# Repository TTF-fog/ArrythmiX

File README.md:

# Main Repo
> For Blueprint Reviewers, [Final Version](Hardware/CAD/the_last_one.step) is what our end CAD model is. Design is goose.f3d present in the same file. BOM is present in root dir, [table format](#BOM) (collapsed) at bottom of readme and [PCB folder](Hardware/PCB). PCB Folder contains gerbers.zip and design files. Firmware is in [firmware](src) and software in [software](scripts). Everything else is in ML or doc. Check [Sections](#sections) for descriptions. thank you for reviewing our project :)

This is the main repo for the Arryhtmix Project, which aims to develop a novel, end-to-end framework for
the prediction of cardiac events

>
> We have developed a novel end to end pipeline for the prediction of cardiac arrests through machine learning alongside a medical device to facilitate the collection of data for the model.
>
>The initial process takes place on the device. The single-lead AD8232 Sensor with integrated hardware high pass and low pass filters collects ECG Data from one lead with one electrode for common mode rejection. The data is read at a rate of 360 Hz by the nRF52840 using a 12-bit ADC and concurrently denoised through an integrated LSM6DS3. While the device is idle, it is kept in deep sleep mode, significantly reducing power consumption.
>Upon the collection of 10 data points, the buffer is dispatched using BLE to the host device.
> 
>Upon being dispatched to the host device, two models are run on it. First, an Arrhythmia classification model based on the MIT-BIH dataset and architected with a BiLSTM and Random Forest classifier returns a dataclass which describes the type of arrhythmia if any. Secondly, a novel hybrid CNN-LSTM model trained on the Sudden Cardiac Arrest Holter Database predicts ventricular fibrillation risk across four temporal categories. The models have been quantised for edge deployment and offer platform flexibility. A f-score of 99 percent and of 85 percent is obtained from both models respectively.
>
- ISEF Abstract
### Sections
- [Scripts](scripts)
  - [Miscellaneous](scripts/misc)
    - mixture of normal and vibecoded scripts made for testing
  - [Rerun](scripts/rerun)
    - Scripts and Blueprints for the [Rerun](https://rerun.io) visualizer
- [Hardware](Hardware)
  - [PCB Documents](Hardware/PCB)
  - [CAD Files](Hardware/CAD)
    - all of these are from some iteration or the other, but they should represent the totality of our cad.
    - [Final Version](Hardware/CAD/the_last_one.step) is what our end model is. Design is goose.f3d present in the same file
- [Firmware](src)
  - firmware for the device
- [ML](ML)
  - Our own model training stuff, and tweaked versions of other's
- [Documentation](Doc) 
  - Extra stuff relating to the project. Will add slide decks soon:tm:
### Images 
<details>

<summary> Machine Learning </summary>

> Confusion Matrix

<br>

> train and valuation graphs

<br>

</details>

<details>

<summary>Software</summary>

Machine

<br>

</details>

<details>

<summary>Hardware</summary>

> unsoldered, sorry for bad quality

<br>

</details>

<details>

<summary>CAD Models</summary>

> click to see preview
</details>

### Bill Of Materials
<details id="BOM">

<summary> Bill Of Materials for PCB</summary>

| JLCPCB BOM Tool - BOM Matching           |                   |                    |                                                                |               |                    |                    |                                                                                                                                                           |               |                                                                                                                                                                                  |                                                            |                                                                                                                       |                   |                                                                           |          |     |           |                 |
|------------------------------------------|-------------------|--------------------|----------------------------------------------------------------|---------------|--------------------|--------------------|-----------------------------------------------------------------------------------------------------------------------------------------------------------|---------------|----------------------------------------------------------------------------------------------------------------------------------------------------------------------------------|------------------------------------------------------------|-----------------------------------------------------------------------------------------------------------------------|-------------------|---------------------------------------------------------------------------|----------|-----|-----------|-----------------|
| BOM name：bom-JLCPCB Assembly Order.xlsx |                   |                    | Download Time：2025-12-03 19:28:29                             |               |                    |                    | * Our matching results are updated in real-time, but stock and prices may change.  If it's been over 24 hours, please re-match before placing your order. |               |                                                                                                                                                                                  |                                                            |                                                                                                                       |                   |                                                                           |          |     |           |                 |
| PCB Assembled Qty：5                     |                   |                    | Est. Total Price：11.8136                                      |               |                    |                    |                                                                                                                                                           |               |                                                                                                                                                                                  |                                                            |                                                                                                                       |                   |                                                                           |          |     |           |                 |
| Your BOM                                 |                   |                    |                                                                |               | Matched Parts      |                    |                                                                                                                                                           |               |                                                                                                                                                                                  |                                                            |                                                                                                                       | Order Information |                                                                           |          |     |           |                 |
| Top Designator                           | Bottom Designator | Comment            | Footprint                                                      | JLCPCB Part # | Matches            | Part #             | Manufacturer                                                                                                                                              | Footprint     | Description                                                                                                                                                                      | Category                                                   | Warning                                                                                                               | JLCPCB Part #     | Product link                                                              | Lib Type | Qty | Source    | Total Price ($) |
| C2                                       |                   | 1nF                | C_0201_0603Metric                                              |               | Select by Customer | 0201B102K500NT     | FH (Guangdong Fenghua Advanced Tech)                                                                                                                      | 0201          | 1nF 50V X7R ±10% 0201 Multilayer Ceramic Capacitors MLCC - SMD/SMT ROHS                                                                                                          | Multilayer Ceramic Capacitors MLCC - SMD/SMT               |                                                                                                                       | C66942            | https://jlcpcb.com/partdetail/68029-0201B102K500NT/C66942                 | Extended | 20  | 20 JLCPCB | 0.014           |
| C5                                       |                   | 1.5nF              | C_0201_0603Metric                                              |               | Select by Customer | GRM033R71C152KA01D | Murata Electronics                                                                                                                                        | 0201          | 1.5nF 16V X7R ±10% 0201 Multilayer Ceramic Capacitors MLCC - SMD/SMT ROHS                                                                                                        | Multilayer Ceramic Capacitors MLCC - SMD/SMT               |                                                                                                                       | C161482           | https://jlcpcb.com/partdetail/172863-GRM033R71C152KA01D/C161482           | Extended | 20  | 20 JLCPCB | 0.05            |
| C6                                       |                   | 10nF               | C_0201_0603Metric                                              |               | Select by Customer | GRM033R61E103KA12D | Murata Electronics                                                                                                                                        | 0201          | 10nF 25V X5R ±10% 0201 Multilayer Ceramic Capacitors MLCC - SMD/SMT ROHS                                                                                                         | Multilayer Ceramic Capacitors MLCC - SMD/SMT               |                                                                                                                       | C76938            | https://jlcpcb.com/partdetail/MurataElectronics-GRM033R61E103KA12D/C76938 | Extended | 20  | 20 JLCPCB | 0.036           |
| C7,C1                                    |                   | 0.33uF             | C_0201_0603Metric                                              |               | Select by Customer | GRM033R61E334KE15D | Murata Electronics                                                                                                                                        | 0201          | 25V 330nF ±10% 0201 Multilayer Ceramic Capacitors MLCC - SMD/SMT ROHS                                                                                                            | Multilayer Ceramic Capacitors MLCC - SMD/SMT               | 1.The comment (GRM033R61E334KE15D) of this part does not match the one (0.33uF) provided in your BOM. Please confirm; | C723889           | https://jlcpcb.com/partdetail/768943-GRM033R61E334KE15D/C723889           | Extended | 20  | 20 JLCPCB | 0.388           |
| C8,C9                                    |                   | 10uF               | C_0402_1005Metric                                              |               | Select by System   | CL05A106MQ5NUNC    | Samsung Electro-Mechanics                                                                                                                                 | 0402          | 10uF 6.3V X5R ±20% 0402 Multilayer Ceramic Capacitors MLCC - SMD/SMT ROHS                                                                                                        | Multilayer Ceramic Capacitors MLCC - SMD/SMT               |                                                                                                                       | C15525            | https://jlcpcb.com/partdetail/16204-CL05A106MQ5NUNC/C15525                | Basic    | 20  | 20 JLCPCB | 0.09            |
| C10,C4,C3                                |                   | 0.1uF              | C_0201_0603Metric                                              |               | Select by Customer | CL03A104KP3NNNC    | Samsung Electro-Mechanics                                                                                                                                 | 0201          | 100nF 10V X5R ±10% 0201 Multilayer Ceramic Capacitors MLCC - SMD/SMT ROHS                                                                                                        | Multilayer Ceramic Capacitors MLCC - SMD/SMT               | 1.The comment (CL03A104KP3NNNC) of this part does not match the one (0.1uF) provided in your BOM. Please confirm;     | C49062            | https://jlcpcb.com/partdetail/50070-CL03A104KP3NNNC/C49062                | Extended | 20  | 20 JLCPCB | 0.026           |
| D1                                       |                   | LED                | LED_0603_1608Metric                                            |               | Unconfirmed        | KT-0603R           | Hubei KENTO Elec                                                                                                                                          | 0603          | -40℃~+85℃ 120° 2.4V 20mA 300mcd 40mW 615nm~630nm 645nm Red Water Clear 0603 LED Indication - Discrete ROHS                                                                       | LED Indication - Discrete                                  | 1.The comment (KT-0603R) of this part does not match the one (LED) provided in your BOM. Please confirm;              | C2286             | https://jlcpcb.com/partdetail/Hubei_KENTOElec-KT0603R/C2286               | Basic    | 20  | 20 JLCPCB | 0.112           |
| R1,R4,R7,R5,R6,R15                       |                   | 10M惟              | R_0201_0603Metric                                              |               | Select by Customer | RTT01106JTH        | RALEC                                                                                                                                                     | 0201          | -55℃~+125℃ 10MΩ 25V 50mW Thick Film Resistor ±200ppm/℃ ±5% 0201 Chip Resistor - Surface Mount ROHS                                                                               | Chip Resistor - Surface Mount                              | 1.The comment (RTT01106JTH) of this part does not match the one (10M惟) provided in your BOM. Please confirm;         | C158867           | https://jlcpcb.com/partdetail/RALEC-RTT01106JTH/C158867                   | Extended | 22  | 22 JLCPCB | 0.0198          |
| R3,R2                                    |                   | 180k惟             | R_0201_0603Metric                                              |               | Select by Customer | RTT01184JTH        | RALEC                                                                                                                                                     | 0201          | -55℃~+125℃ 180kΩ 25V 50mW Thick Film Resistor ±200ppm/℃ ±5% 0201 Chip Resistor - Surface Mount ROHS                                                                              | Chip Resistor - Surface Mount                              | 1.The comment (RTT01184JTH) of this part does not match the one (180k惟) provided in your BOM. Please confirm;        | C158738           | https://jlcpcb.com/partdetail/RALEC-RTT01184JTH/C158738                   | Extended | 20  | 20 JLCPCB | 0.068           |
| R8                                       |                   | 360k               | R_0201_0603Metric                                              |               | Select by Customer | RTT01364JTH        | RALEC                                                                                                                                                     | 0201          | -55℃~+125℃ 25V 360kΩ 50mW Thick Film Resistor ±200ppm/℃ ±5% 0201 Chip Resistor - Surface Mount ROHS                                                                              | Chip Resistor - Surface Mount                              | 1.The comment (RTT01364JTH) of this part does not match the one (360k) provided in your BOM. Please confirm;          | C158574           | https://jlcpcb.com/partdetail/RALEC-RTT01364JTH/C158574                   | Extended | 20  | 20 JLCPCB | 0.022           |
| R9,R13,R14                               |                   | 1M惟               | R_0201_0603Metric                                              |               | Select by Customer | RTT011004FTH       | RALEC                                                                                                                                                     | 0201          | -55℃~+125℃ 1MΩ 25V 50mW Thick Film Resistor ±1% ±200ppm/℃ 0201 Chip Resistor - Surface Mount ROHS                                                                                | Chip Resistor - Surface Mount                              | 1.The comment (RTT011004FTH) of this part does not match the one (1M惟) provided in your BOM. Please confirm;         | C102686           | https://jlcpcb.com/partdetail/RALEC-RTT011004FTH/C102686                  | Extended | 20  | 20 JLCPCB | 0.018           |
| R12                                      |                   | 100k惟             | R_0201_0603Metric                                              |               | Select by Customer | CR0201FH1003G      | LIZ Elec                                                                                                                                                  | 0201          | -55℃~+125℃ 100kΩ 25V 50mW Thick Film Resistor ±1% ±250ppm/℃ 0201 Chip Resistor - Surface Mount ROHS                                                                              | Chip Resistor - Surface Mount                              | 1.The comment (CR0201FH1003G) of this part does not match the one (100k惟) provided in your BOM. Please confirm;      | C100127           | https://jlcpcb.com/partdetail/LIZElec-CR0201FH1003G/C100127               | Extended | 20  | 20 JLCPCB | 0.016           |
| R16                                      |                   | 1.4m惟             | R_0201_0603Metric                                              |               | Select by Customer | 0201WMF1404TEE     | UNI-ROYAL(Uniroyal Elec)                                                                                                                                  | 0201          | -55℃~+155℃ 1.4MΩ 25V 50mW Thick Film Resistor ±1% ±200ppm/℃ 0201 Chip Resistor - Surface Mount ROHS                                                                              | Chip Resistor - Surface Mount                              |                                                                                                                       | C423737           | https://jlcpcb.com/partdetail/416687-0201WMF1404TEE/C423737               | Extended | 20  | 20 JLCPCB | 0.028           |
| R19                                      |                   | 1k                 | R_0402_1005Metric                                              |               | Select by Customer | 0402WGF1001TCE     | UNI-ROYAL(Uniroyal Elec)                                                                                                                                  | 0402          | -55℃~+155℃ 1kΩ 50V 62.5mW Thick Film Resistor ±1% ±100ppm/℃ 0402 Chip Resistor - Surface Mount ROHS                                                                              | Chip Resistor - Surface Mount                              | 1.The comment (0402WGF1001TCE) of this part does not match the one (1k) provided in your BOM. Please confirm;         | C11702            | https://jlcpcb.com/partdetail/12256-0402WGF1001TCE/C11702                 | Basic    | 20  | 20 JLCPCB | 0.012           |
| R21,R20                                  |                   | 2.2K               | R_0402_1005Metric                                              |               | Select by Customer | 0402WGF2201TCE     | UNI-ROYAL(Uniroyal Elec)                                                                                                                                  | 0402          | -55℃~+155℃ 2.2kΩ 50V 62.5mW Thick Film Resistor ±1% ±100ppm/℃ 0402 Chip Resistor - Surface Mount ROHS                                                                            | Chip Resistor - Surface Mount                              | 1.The comment (0402WGF2201TCE) of this part does not match the one (2.2K) provided in your BOM. Please confirm;       | C25879            | https://jlcpcb.com/partdetail/26622-0402WGF2201TCE/C25879                 | Basic    | 20  | 20 JLCPCB | 0.012           |
| U2                                       |                   | AD8232             | LFCSP_20                                                       |               | Unconfirmed        | AD8232ACPZ-R7      | Analog Devices                                                                                                                                            | LFCSP-20(4x4) | -40℃~+85℃ 12ppm/℃ 170uA 2V~3.5V LFCSP-20(4x4) Analog Front End (AFE) ROHS                                                                                                        | Analog To Digital Converters (ADC)                         | 1.The comment (AD8232ACPZ-R7) of this part does not match the one (AD8232) provided in your BOM. Please confirm;      | C43216            | https://jlcpcb.com/partdetail/AnalogDevices-AD8232ACPZR7/C43216           | Extended | 2   | 2 JLCPCB  | 5.715           |
| U3                                       |                   | NCP1117-3.3_SOT223 | SOT-223-3_TabPin2                                              |               | Select by Customer | AMS1117-3.3        | Advanced Monolithic Systems                                                                                                                               | SOT-223       | -40℃~+125℃ 0.003%Vout 1 1.1V@(800mA) 16V 1A 3.3V 5mA 72dB@(120Hz) Fixed Over Current Protection Positive SOT-223 Voltage Regulators - Linear, Low Drop Out (LDO) Regulators ROHS | Voltage Regulators - Linear, Low Drop Out (LDO) Regulators |                                                                                                                       | C6186             | https://jlcpcb.com/partdetail/Advanced_MonolithicSystems-AMS1117_33/C6186 | Basic    | 2   | 2 JLCPCB  | 0.3178          |
| U4                                       |                   | MAX17048G_T10      | SON50P200X200X80-9N                                            |               | Select by System   | MAX17048G+T10      | Analog Devices Inc./Maxim Integrated                                                                                                                      | DFN-8-EP(2x2) | -40℃~+85℃ 1 2.5V~4.5V 3uA I2C Lithium Battery Not Supported Not Supported DFN-8-EP(2x2) Battery Management ROHS                                                                  | Battery Management                                         |                                                                                                                       | C2682616          | https://jlcpcb.com/partdetail/2777647-MAX17048GT10/C2682616               | Extended | 2   | 2 JLCPCB  | 4.869           |
| J1                                       |                   | DNP                | PinSocket_1x04_P1.27mm_Vertical                                |               | No matches         | No Part Selected   |                                                                                                                                                           |               |                                                                                                                                                                                  |                                                            |                                                                                                                       |                   |                                                                           |          |     |           |                 |
| J2                                       |                   | DNP                | PinSocket_1x02_P2.54mm_Vertical                                |               | No matches         | No Part Selected   |                                                                                                                                                           |               |                                                                                                                                                                                  |                                                            |                                                                                                                       |                   |                                                                           |          |     |           |                 |
| J3                                       |                   | DNP                | PinHeader_1x03_P2.54mm_Vertical                                |               | No matches         | No Part Selected   |                                                                                                                                                           |               |                                                                                                                                                                                  |                                                            |                                                                                                                       |                   |                                                                           |          |     |           |                 |
| SW1                                      |                   | SW_SPST            | SW_DIP_SPSTx01_Slide_6.7x4.1mm_W6.73mm_P2.54mm_LowProfile_JPin |               | No matches         | No Part Selected   |                                                                                                                                                           |               |                                                                                                                                                                                  |                                                            |                                                                                                                       |                   |                                                                           |          |     |           |                 |
| U1                                       |                   | XIAO-nRF52840-SMD  | XIAO-nRF52840-SMD                                              |               | No matches         | No Part Selected   |                                                                                                                                                           |               |                                                                                                                                                                                  |                                                            |                                                                                                                       |                   |                                                                           |          |     |           |                 |

</details>

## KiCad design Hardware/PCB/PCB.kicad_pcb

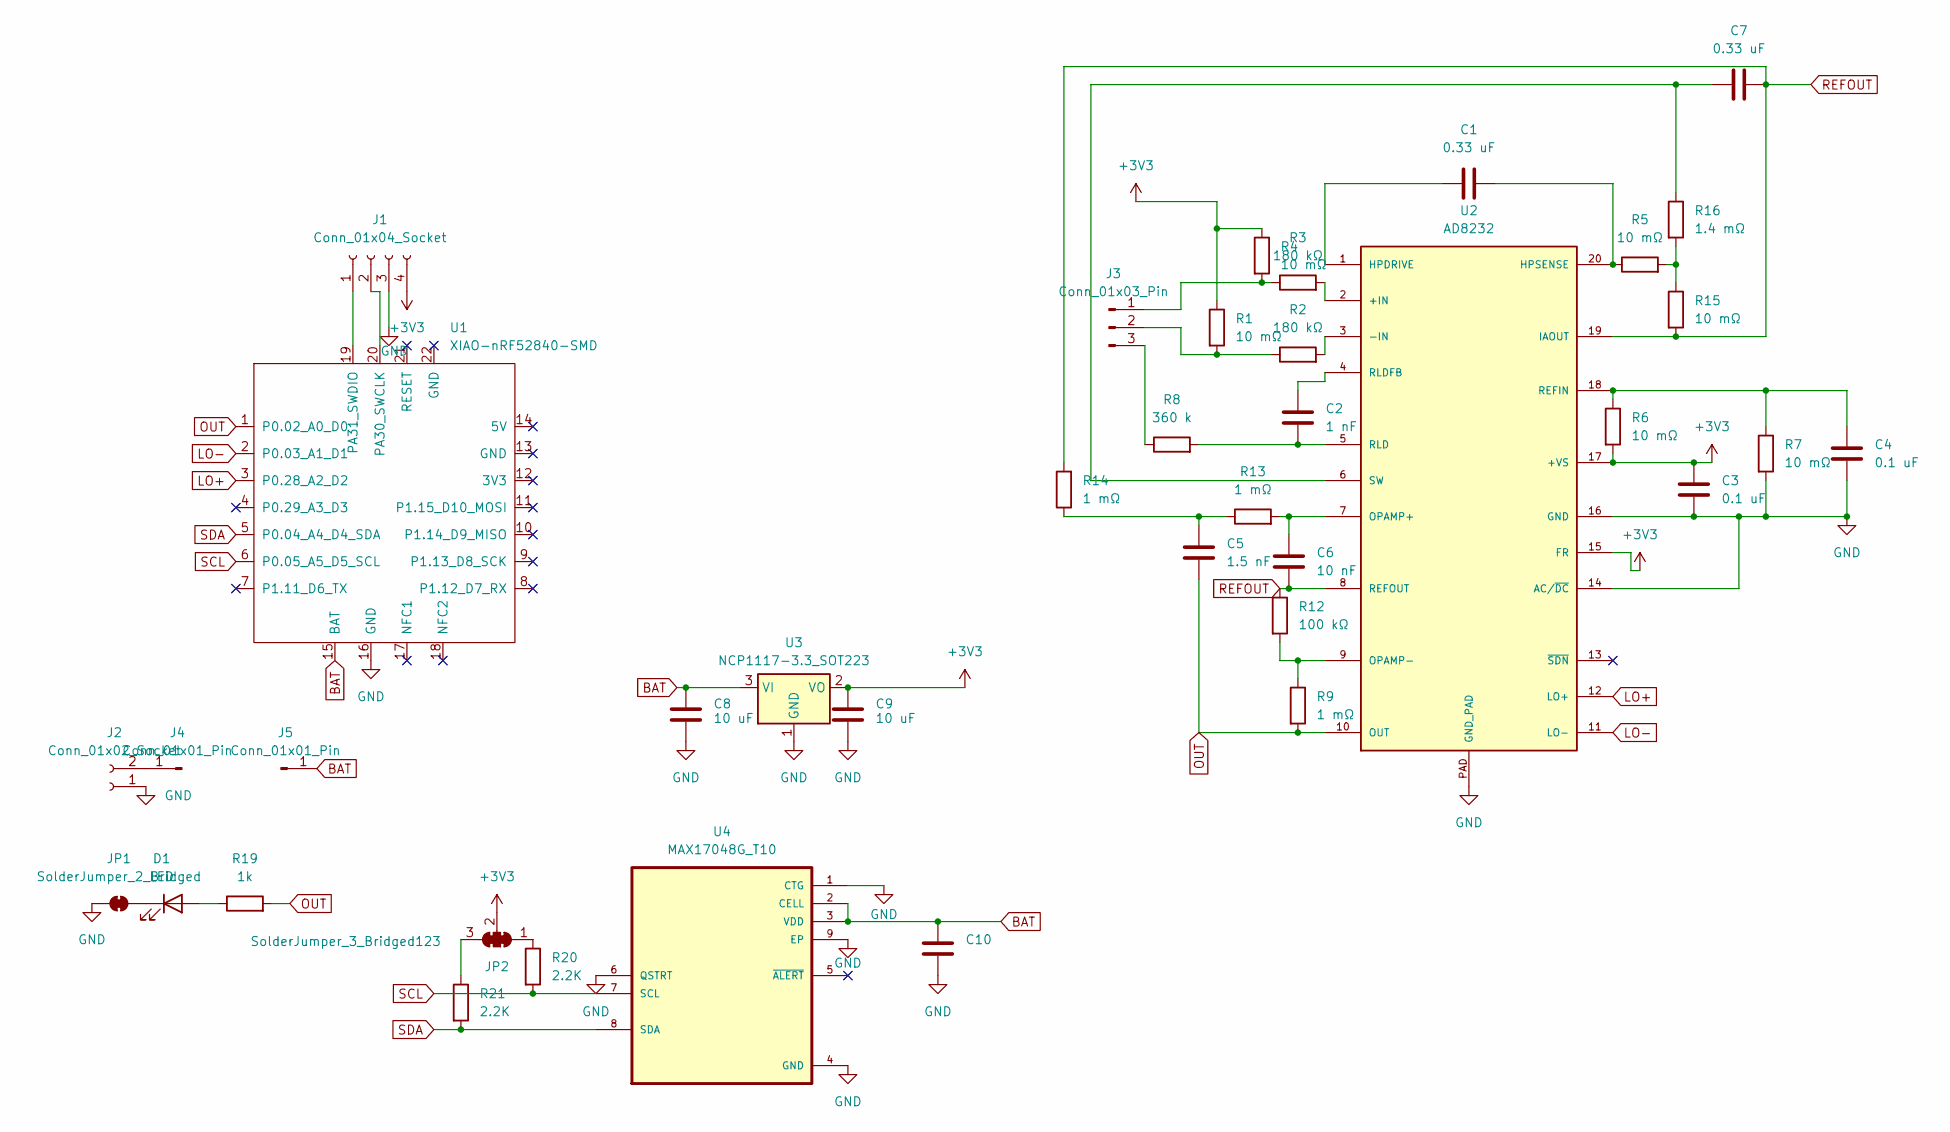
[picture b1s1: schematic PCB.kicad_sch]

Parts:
C1, C7: 0.33 uF; C_0201_0603Metric
C2: 1 nF; C_0201_0603Metric
C3, C4, C10: 0.1 uF; C_0201_0603Metric
C5: 1.5 nF; C_0201_0603Metric
C6: 10 nF; C_0201_0603Metric
C8, C9: 10 uF; C_0402_1005Metric
D1: LED; LED_0603_1608Metric
J1: Conn_01x04_Socket; PinSocket_1x04_P1.27mm_Vertical
J2: Conn_01x02_Socket; PinSocket_1x02_P2.54mm_Vertical
J3: Conn_01x03_Pin; PinHeader_1x03_P2.54mm_Vertical
J4, J5: Conn_01x01_Pin; PinSocket_1x01_P2.54mm_Vertical
JP1: SolderJumper_2_Bridged; SolderJumper-2_P1.3mm_Bridged2Bar_RoundedPad1.0x1.5mm
JP2: SolderJumper_3_Bridged123; SolderJumper-3_P1.3mm_Open_Pad1.0x1.5mm_NumberLabels
R1, R4, R5, R6, R7, R15: 10 mΩ; R_0201_0603Metric
R2, R3: 180 kΩ; R_0201_0603Metric
R8: 360 k; R_0201_0603Metric
R9, R13, R14: 1 mΩ; R_0201_0603Metric
R12: 100 kΩ; R_0201_0603Metric
R16: 1.4 mΩ; R_0201_0603Metric
R19: 1k; R_0402_1005Metric
R20, R21: 2.2K; R_0402_1005Metric
U1: XIAO-nRF52840-SMD
U2: AD8232; LFCSP_20
U3: NCP1117-3.3_SOT223; SOT-223-3_TabPin2
U4: MAX17048G_T10; SON50P200X200X80-9N

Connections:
+3V3: C3.2, C9.1, J1.4, JP2.2 (C), R1.1, R4.1, R6.2, U2.15 (FR), U2.17 (+VS), U3.2 (VO)
BAT: C8.1, C10.2, J5.1, U1.15 (BAT), U3.3 (VI), U4.2 (CELL), U4.3 (VDD)
GND: C3.1, C4.1, C8.2, C9.2, C10.1, J1.3, J2.1, JP1.1 (A), R7.2, U1.16 (GND), U2.14 (AC/~DC), U2.16 (GND), U2.PAD (GND_PAD), U3.1 (GND), U4.1 (CTG), U4.4 (GND), U4.6 (QSTRT), U4.9 (EP)
LO+: U1.3 (P0.28_A2_D2), U2.12 (LO+)
LO-: U1.2 (P0.03_A1_D1), U2.11 (LO-)
unnamed: C5.2, R13.1, R14.1
unnamed: D1.2 (A), R19.1
unnamed: D1.1 (K), JP1.2 (B)
unnamed: J1.1, U1.19 (PA31_SWDIO)
unnamed: J1.2, U1.20 (PA30_SWCLK)
unnamed: J2.2, J4.1
unnamed: J3.1, R3.1, R4.2
unnamed: J3.2, R1.2, R2.1
unnamed: J3.3, R8.1
unnamed: JP2.1 (A), R20.1
unnamed: JP2.3 (B), R21.1
unnamed: R5.2, R15.1, R16.2
unnamed: R3.2, U2.2 (+IN)
unnamed: R2.2, U2.3 (-IN)
unnamed: C1.1, U2.1 (HPDRIVE)
unnamed: C1.2, R5.1, U2.20 (HPSENSE)
unnamed: C6.2, R13.2, U2.7 (OPAMP+)
unnamed: R9.1, R12.2, U2.9 (OPAMP-)
unnamed: C4.2, R6.1, R7.1, U2.18 (REFIN)
unnamed: C2.2, R8.2, U2.5 (RLD)
unnamed: C2.1, U2.4 (RLDFB)
unnamed: C7.1, R16.1, U2.6 (SW)
OUT: C5.1, R9.2, R19.2, U1.1 (P0.02_A0_D0), U2.10 (OUT)
REFOUT: C6.1, C7.2, R12.1, R14.2, R15.2, U2.8 (REFOUT), U2.19 (IAOUT)
SCL: R20.2, U1.6 (P0.05_A5_D5_SCL), U4.7 (SCL)
SDA: R21.2, U1.5 (P0.04_A4_D4_SDA), U4.8 (SDA)

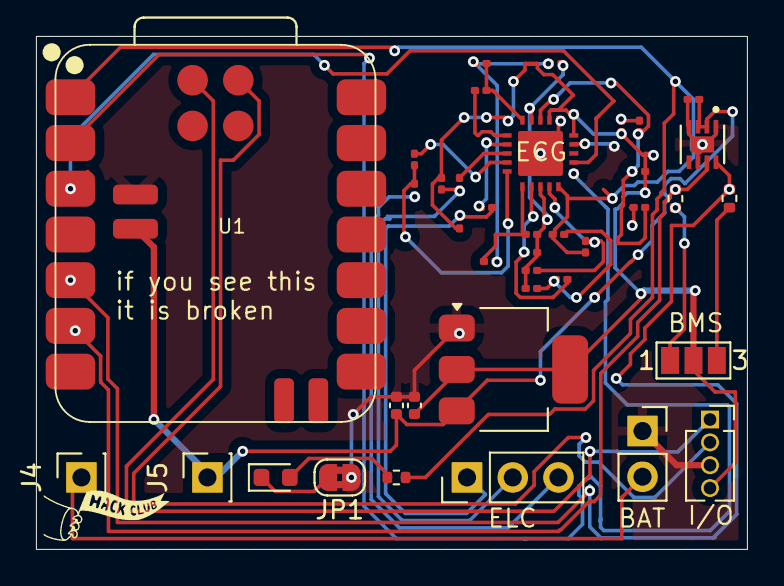
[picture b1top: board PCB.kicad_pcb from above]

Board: 4 copper layers, 39.5 x 28.5 mm, 39 parts (0 on the bottom side), 31 nets.

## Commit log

2024-10-05 aaaaaaaaaaaaaaaaaaaaaaaaaaaaaaaaaaaaaaaa
2025-10-08 add nrf52840 code
2025-10-08 add python scripts
2025-10-13 add latest ML, dashboard stuff
2025-10-14 long long years of suffering past
2025-11-07 sleep instead of busy waiting for better power consumption, need to transmit IMU
2025-11-07 add buffering
2025-11-14 cleanup repo, add README.md
2025-11-14 w
    w
2025-11-17 setup basic zephyr functionality
2025-11-19 adc readring
2025-11-19 i cooked
2026-01-20 add pcb files
2026-01-20 wonga
2026-02-12 typo
2026-02-12 gian refactor
2026-02-12 fix table
2026-02-12 fixes and reformats
2026-02-12 puh ceh buh foh ld dher
2026-03-02 fix: last typo
2026-03-03 wait a second
2026-03-04 updates to make it cleaner
2026-03-04 Enhance navigation instructions in README
    Updated README to improve navigation instructions.
2026-03-04 Fix formatting and update ISEF Abstract section
2026-03-04 stop bloating up main with stupid commits
    * updates to make it cleaner
    * Update README.md
    * Enhance navigation instructions in README
    Updated README to improve navigation instructions.
    * Fix formatting and update ISEF Abstract section
    ---------
2026-03-05 compliance with ai
2026-03-05 Readme (#3)
    * updates to make it cleaner
    * Update README.md
    * Enhance navigation instructions in README
    Updated README to improve navigation instructions.
    * Fix formatting and update ISEF Abstract section
    * compliance with ai
2026-03-05 aaa iife:w
